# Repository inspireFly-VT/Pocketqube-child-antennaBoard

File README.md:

# Pocketqube-child-antennaBoard
~430 MHz antenna board, integrating a RFM98W transceiver.

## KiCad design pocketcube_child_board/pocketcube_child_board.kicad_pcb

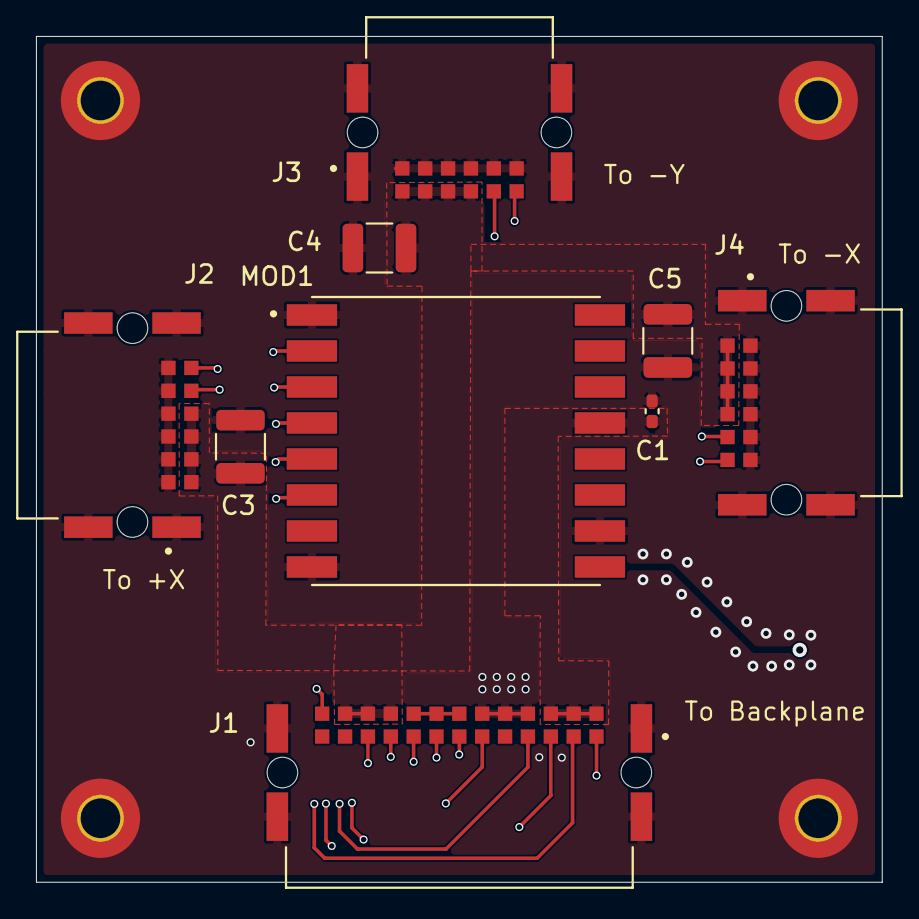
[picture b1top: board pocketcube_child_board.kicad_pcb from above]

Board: 4 copper layers, 47.0 x 47.0 mm, 14 parts (1 on the bottom side), 16 nets.

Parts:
AE1: Antenna; Tape Antenna
C1: 100nF; C_0402_1005Metric_Pad0.74x0.62mm_HandSolder
C3, C4, C5: 22uF; C_1210_3225Metric
H1, H2, H3, H4: MountingHole_Pad; MountingHole_2.2mm_M2_Pad_TopBottom
J1: M55-7102642R; HARWIN_M55-7102642R
J2, J3, J4: M55-7101242R; HARWIN_M55-7101242R
MOD1: RFM98W-433S2; XCVR_RFM98W-433S2

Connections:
+3.3V: C1.2, J1.B1, J1.B2, J1.B3, MOD1.13 (3.3V)
/ANTENNA_TRACE: AE1.1 (A_1), MOD1.9 (ANT)
ANT_SPI2_MISO: J1.A2, MOD1.2 (MISO)
ANT_SPI2_MOSI: J1.A1, MOD1.3 (MOSI)
ANT_SPI2_NSS: J1.A3, MOD1.5 (NSS)
ANT_SPI2_SCK: J1.A4, MOD1.4 (SCK)
BAT_VOLTAGE: J1.B7, J1.B8, J1.B9
EXTERNAL_VOLTAGE: C3.2, C4.2, C5.2, J1.B10, J1.B11, J1.B12, J2.B1, J2.B2, J2.B3, J2.B4, J3.B1, J3.B2, J3.B3, J3.B4, J4.B1, J4.B2, J4.B3, J4.B4
GND: C1.1, C3.1, C4.1, C5.1, H1.1 (1_1), H2.1 (1_1), H3.1 (1_1), H4.1 (1_1), J1.B4, J1.B5, J1.B6, J1.SH1, J1.SH2, J1.SH3, J1.SH4, J2.A1, J2.A2, J2.A3, J2.A4, J2.A5, J2.A6, J2.SH1, J2.SH2, J2.SH3, J2.SH4, J3.A1, J3.A2, J3.A3, J3.A4, J3.A5, J3.A6, J3.SH1, J3.SH2, J3.SH3, J3.SH4, J4.A1, J4.A2, J4.A3, J4.A4, J4.A5, J4.A6, J4.SH1, J4.SH2, J4.SH3, J4.SH4, MOD1.1 (GND), MOD1.8 (GND__2), MOD1.10 (GND__4)
I2C1_SCL: J1.A7, J2.B5
I2C1_SDA: J1.A6, J2.B6
I2C2_SCL: J1.A9, J3.B5
I2C2_SDA: J1.A8, J3.B6
I2C3_SCL: J1.A11, J4.B5
I2C3_SDA: J1.A10, J4.B6
RFM_RESET: J1.B13, MOD1.6 (RESET)

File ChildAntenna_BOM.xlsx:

Distributor | Part Number | Part Description | Quantity Per Board
Digikey | GRM32ER71E226KE15L | CAP CER 22UF 25V X7R 1210 | 3
Digikey | CL05B104KA5NNNC | CAP CER 0.1UF 25V X7R 0402 | 1
Mouser | RFM98W-433S2 | RFM98W-433S2 | 1
Digikey | M55-7101242R | CONN HEADER SMD R/A 12POS 1.27MM | 3
Digikey | M55-7102642R | CONN HEADER SMD R/A 26POS 1.27MM | 1

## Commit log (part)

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2025-10-09 Sending in LOCK
2025-10-14 Creating KiCad Project
    Created the KiCad project for the child board. Did not update the LOCK file as I have not edited/worked on anything on the schematic/PCB
2025-10-14 Deletion of unecessary "Untitled"file
2025-10-14 Done working
2025-10-15 Beginning to work on antenna schematic
2025-10-15 Finished Working
2025-10-16 Fixed footprints
2025-10-23 Added to the task list
2025-10-23 Added new connector to PCB
2025-10-23 Added Notes to tasklist
2025-10-26 Locking for review
2025-10-26 Adding cap and finishing review
    See teams message
2025-11-02 11/2 via stitching v0.1
2025-11-02 Testing push capabilities for current folder
2025-11-02 Reverting Changes
2025-11-02 11/2 via attempt
2025-11-02 Edited Tasklist
2025-11-04 Edited PCB Layout & Rearranged Pins
    I restructured the layout of the PCB due to traces going under the components, I also changed the pin order of the connector to add with routing
2025-11-05 Added SI3477DV-T1-GE3 P-Channel MOSFET to Schematic and PCB
2025-11-05 Integrating P-Channel MOSFET
2025-11-09 implemented pmos
2025-11-09 pmos implementation
2025-11-09 Revert "pmos implementation"
    This reverts commit 559285578e66f978812a0fb110e98bc36d41d9a4.
2025-11-09 PMOS Implementation and Ground Plane
2026-03-10 Pushing Board sizes
2026-03-20 Antenna location changes
2026-03-30 updated antenna traces
2026-04-01 stuff from HITT
2026-04-12 4 layer board routing
    2 ground layers between front and backplane to increase rf performance, may need to use for routing though
2026-04-19 Pocketcube Monopole Antenna Board - Alex
2026-04-19 A few more changes
2026-04-19 Pushing Routing Changes
2026-05-03 Updates due to changes from backplane
2026-05-04 BOM work + silkscreen
